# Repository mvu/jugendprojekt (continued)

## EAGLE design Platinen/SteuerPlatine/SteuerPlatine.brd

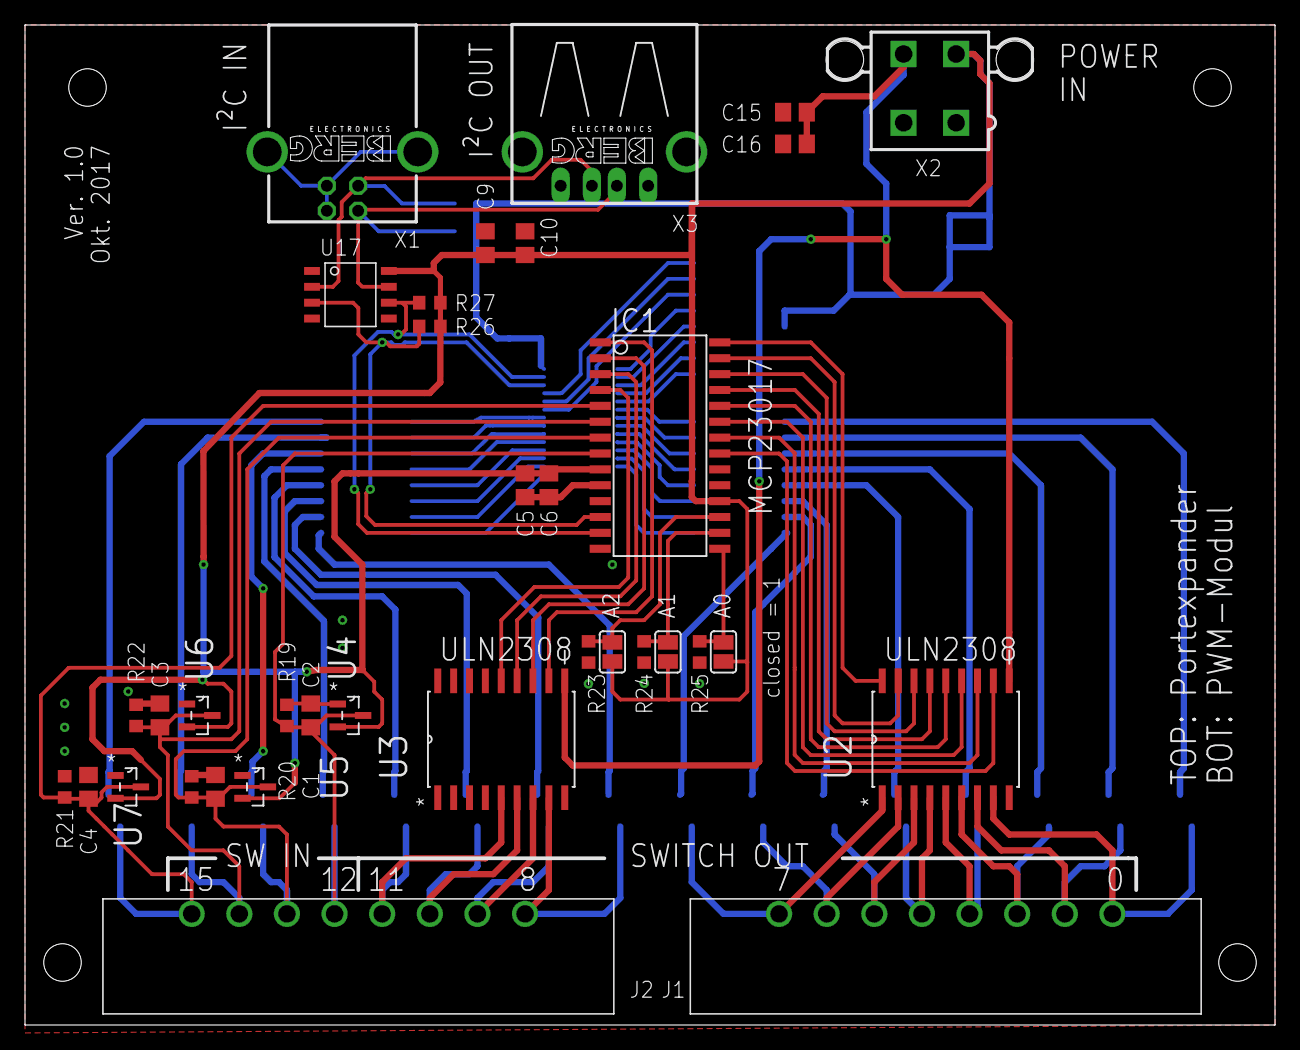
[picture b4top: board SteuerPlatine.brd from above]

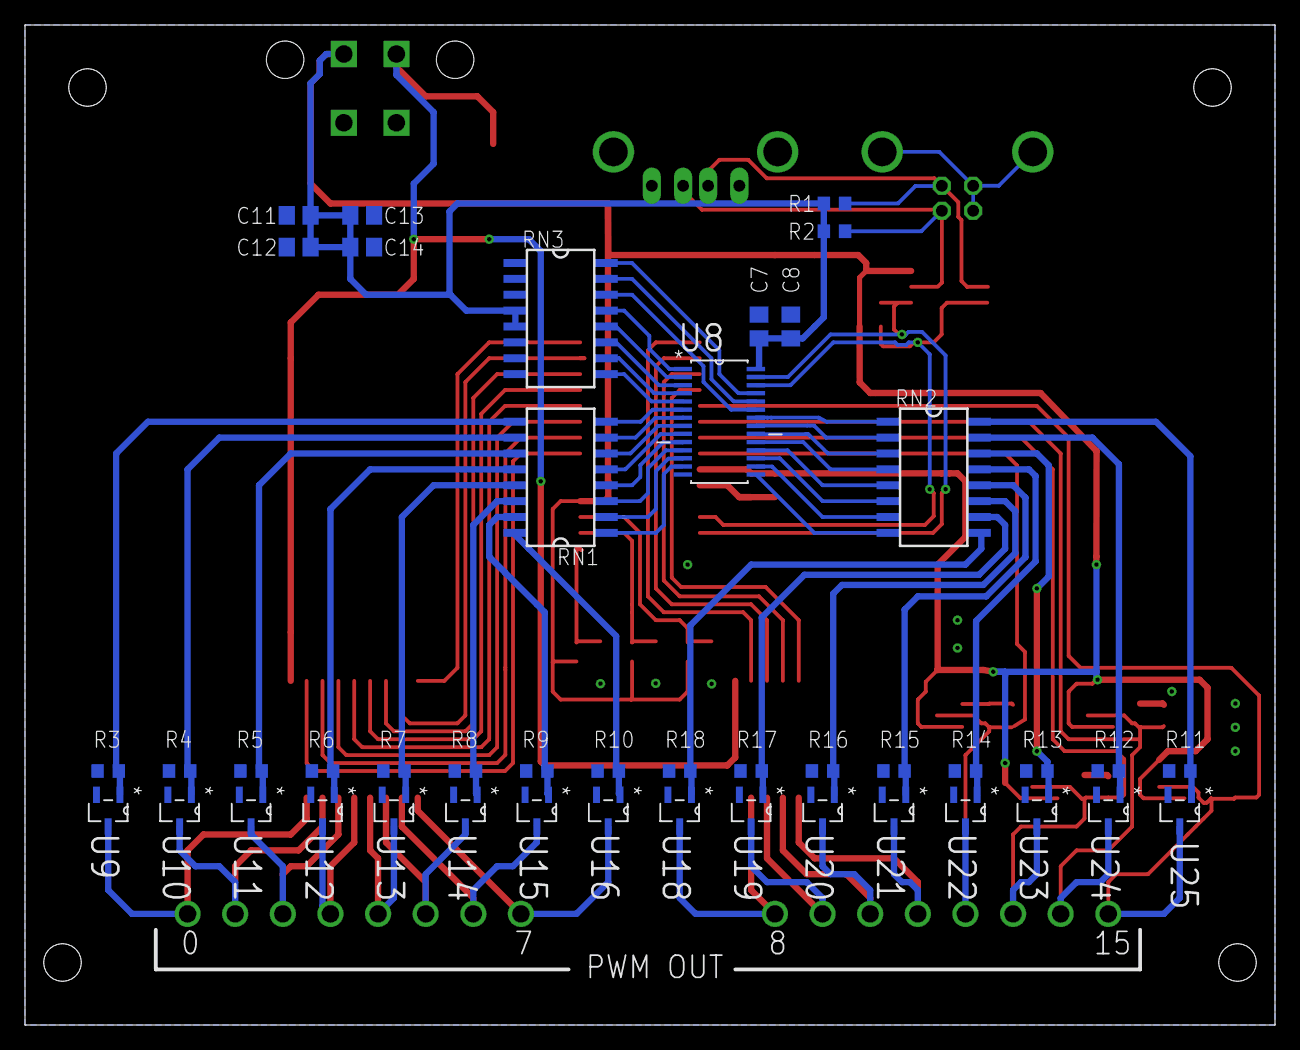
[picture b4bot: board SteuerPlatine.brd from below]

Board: 2 copper layers, 100.0 x 80.0 mm, 79 parts (44 on the bottom side), 78 nets.

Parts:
A0, A1, A2: SJ
C1, C2, C3, C4, C5, C7, C10, C11, C12, C15: 100nF; C0805
C6, C8, C9, C13, C14, C16: 10µF; C0805
IC1: MCP23017SO; SO28W
J1, J2: 691325310008
R1, R2, R3, R4, R5, R6, R7, R8, R9, R10, R11, R12, R13, R14, R15, R16, R17, R18, R26, R27: R0603
R19, R20, R21, R22, R23, R24, R25: 3k; R0603
RN1, RN2, RN3: SOMC16
U2, U3: ULN2803ADW; SOIC127P1030X265-18N
U4, U5, U6, U7: BAV99; SOT91P240X120-3N
U8: PCA9635PW; SOP65P640X110-28N
U9, U10, U11, U12, U13, U14, U15, U16, U18, U19, U20, U21, U22, U23, U24, U25: TSM2306CX; SOT95P280X130-3N
U17: P82B715TD; SOIC-8
X1: PN61729-S
X2: 5566-4
X3: PN87520-S

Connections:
+5V: A0.2, A1.2, A2.2, C5.1, C6.1, C7.1, C8.1, C9.1, C10.1, C11.2, C12.2, C13.2, C14.2, IC1.9, IC1.18, R1.1, R2.1, R26.2, R27.2, RN3.4, RN3.5, U4.2, U5.2, U6.2, U7.2, U8.28, U17.8, X2.3
+12V: C15.1, C16.1, U2.10, U3.10, X2.4
GND: C1.1, C2.1, C3.1, C4.1, C5.2, C6.2, C7.2, C8.2, C9.2, C10.2, C11.1, C12.1, C13.1, C14.1, C15.2, C16.2, IC1.10, R3.1, R4.1, R5.1, R6.1, R7.1, R8.1, R9.1, R10.1, R11.1, R12.1, R13.1, R14.1, R15.1, R16.1, R17.1, R18.1, R19.2, R20.2, R21.2, R22.2, R23.1, R24.1, R25.1, RN3.1, RN3.2, RN3.3, RN3.6, RN3.7, RN3.8, U2.9, U3.9, U4.1, U5.1, U6.1, U7.1, U8.14, U9.2, U10.2, U11.2, U12.2, U13.2, U14.2, U15.2, U16.2, U17.4, U18.2, U19.2, U20.2, U21.2, U22.2, U23.2, U24.2, U25.2, X1.1, X1.4, X1.S1, X1.S2, X2.1, X2.2
unnamed: RN2.1, U8.22
unnamed: RN2.2, U8.21
unnamed: RN2.3, U8.20
unnamed: RN2.4, U8.19
unnamed: RN2.5, U8.18
unnamed: RN2.6, U8.17
unnamed: RN2.7, U8.16
unnamed: RN2.8, U8.15
unnamed: RN1.3, U8.11
unnamed: RN1.2, U8.12
unnamed: RN1.1, U8.13
unnamed: RN1.4, U8.10
unnamed: RN1.5, U8.9
unnamed: RN1.6, U8.8
unnamed: RN1.7, U8.7
unnamed: RN1.8, U8.6
unnamed: IC1.21, U2.11
unnamed: IC1.22, U2.12
unnamed: IC1.23, U2.13
unnamed: IC1.24, U2.14
unnamed: IC1.25, U2.15
unnamed: IC1.26, U2.16
unnamed: IC1.27, U2.17
unnamed: IC1.28, U2.18
unnamed: IC1.1, U3.11
unnamed: IC1.2, U3.12
unnamed: IC1.3, U3.13
unnamed: IC1.4, U3.14
unnamed: RN3.9, U8.5
unnamed: RN3.16, U8.25
unnamed: RN3.15, U8.24
unnamed: RN3.10, U8.4
unnamed: RN3.11, U8.3
unnamed: RN3.12, U8.2
unnamed: RN3.13, U8.1
unnamed: RN3.14, U8.23
unnamed: A2.1, IC1.17, R23.2
unnamed: A1.1, IC1.16, R24.2
unnamed: A0.1, IC1.15, R25.2
unnamed: R2.2, U17.7, X1.2, X3.2
unnamed: R1.2, U17.2, X1.3, X3.3
PWM1: R3.2, RN1.9, U9.1
PWM2: R4.2, RN1.10, U10.1
PWM3: R5.2, RN1.11, U11.1
PWM4: R6.2, RN1.12, U12.1
PWM5: R7.2, RN1.13, U13.1
PWM6: R8.2, RN1.14, U14.1
PWM7: R9.2, RN1.15, U15.1
PWM8: R10.2, RN1.16, U16.1
PWM9: R18.2, RN2.9, U18.1
PWM10: R17.2, RN2.10, U19.1
PWM11: R16.2, RN2.11, U20.1
PWM12: R15.2, RN2.12, U21.1
PWM13: R14.2, RN2.13, U22.1
PWM14: R13.2, RN2.14, U23.1
PWM15: R12.2, RN2.15, U24.1
PWM16: R11.2, RN2.16, U25.1
PWM-OUT1: J1.8, U2.8, U9.3
PWM-OUT2: J1.7, U2.7, U10.3
PWM-OUT3: J1.6, U2.6, U11.3
PWM-OUT4: J1.5, U2.5, U12.3
PWM-OUT5: J1.4, U2.4, U13.3
PWM-OUT6: J1.3, U2.3, U14.3
PWM-OUT7: J1.2, U2.2, U15.3
PWM-OUT8: J1.1, U2.1, U16.3
PWM-OUT9: J2.8, U3.8, U18.3
PWM-OUT10: J2.7, U3.7, U19.3
PWM-OUT11: J2.6, U3.6, U20.3
PWM-OUT12: J2.5, U3.5, U21.3
PWM-OUT13: C2.2, IC1.8, J2.4, R19.1, U4.3, U22.3
PWM-OUT14: C1.2, IC1.7, J2.3, R20.1, U5.3, U23.3
PWM-OUT15: C3.2, IC1.6, J2.2, R22.1, U6.3, U24.3
PWM-OUT16: C4.2, IC1.5, J2.1, R21.1, U7.3, U25.3
SCL: IC1.12, R26.1, U8.26, U17.3
SDA: IC1.13, R27.1, U8.27, U17.6

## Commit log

2016-05-19 Update README.md
    voll krass new changes alter
2016-10-03 Erster commit: control panel
2016-10-03 readme angepasst
2016-10-03 readme geaendert
2017-05-18 Neuster Stand
2017-05-18 Datasheet hinzugefügt
2017-05-18 Code der Aruinos an den RGB-Stripes
2017-05-18 Das Programm der Arduinos an den RGB-Stripes
2017-05-19 Temperatur überwachung über Netzwerk
2017-05-19 Update Netzwerk mit IP vom Raspberry pi
2017-09-30 Beta Version 1.0
    ein gute lauffähiges Programm ohne Slider und Decken RGB
2017-12-12 Update
    Neue Platinen und Dokumentation
2017-12-13 alle Teile von reichelt oder Conrad
2017-12-14 Liste aktualisiert
2017-12-15 CAD-Zeichnungen für Befestigungsplatte erstellt
2017-12-15 CAD-Zeichnung für Befestigungsplatte aktualisiert
2017-12-15 Umfangreiche Neuorganisation der Ordnerstruktur
2017-12-15 Platinen als pdf exportiert
2017-12-15 minor changes
2017-12-20 Stücklist
2017-12-20 Aktualisiert
2017-12-22 Teile aktualisiert
2017-12-27 CAD Zeichnung Befestigung Portexpander erstellt
2018-01-02 Notizen hinzugefügt
2018-01-20 Simulationen hochgeladen
2018-01-20 aktuelles Programm von RaspberryPi hochgeladen
2018-02-16 Slider test mit Netzwerk über UDP
2018-05-08 Update
    Update text und Jugend 2.1
2018-05-26 Mosfet-Treiber simuliert
2018-05-26 Datenblätter hinzugefügt
2018-05-26 .lib aus gitignore entfernt, um LTSpice-Modelle zu versionieren
2018-05-27 ein paar libraries für LT-Spice hinzugefügt
2018-05-27 Mosfet Treiber Update
2018-05-27 kleinigkeiten
2018-05-27 .zip datei entpackt
2018-05-29 Teile für Mosfet-Treiber 2.0 in Bestückungsliste eingetragen
2018-05-29 Arduino-Test-Programm zur PWM-Generation hinzugefügt
2018-05-29 Mosfet-Treiber 2.0 PCB-Layout finalisiert
2018-06-04 Mosfet Treiber fertig gestellt
2018-06-05 Befestigungsloch verschoben
2018-06-05 Dateien in Ordner zusammengefasst
2018-06-05 CAD für Befestigungsplatte der Mosfet-Treiber Ver 2.0 erstellt
2018-06-05 gerber Files erzeugt
2018-06-12 Bestückungsliste für Mosfettreiber Ver. 2 erstellt
2018-07-28 Slider_UDP.ino in eigenen Ordner verschoben; Arduino IDE braucht das
2018-07-28 weitere Datenblätter hinzugefügt
2018-07-28 echte 0% Pulsbreite eingebaut
2018-07-28 Hauptlichttreiber fertig gestellt
2019-01-14 .gitignore für LT-Spice angepasst
2019-01-14 update2
2019-01-15 Grundstein für Version 3.0 gelegt
2019-01-15 Doxygen intergriert
2019-01-15 MainWindow aus altem Projekt in Startseite umgezogen
2019-01-15 Dateien nach model und view getrennt, low lvel hardware Zugriff begonnen
2019-01-15 Dokumentation um Ordner- und Dateibeschreibungen erweitert
2019-01-16 Einstellungen für QtCreator für cross-compile und ausführung via RDP
2019-01-17 .pro.shared Datei entfernt, da unnötig
2019-01-17 Bug entdeckt und kommentiert
2019-01-17 Licht- und Medien-Menü umgezogen
2019-01-17 Systemstatus GUI umgezogen
2019-01-17 EinstellungTheke-Gui umgezogen
2019-01-17 fehlende Dateien EinstellungTheke-Gui umgezogen
2019-01-17 fixed merge conflict in .pro
2019-01-17 GUI Einstellung RGB Wand umgezogen
2019-01-18 Passwort GUI umgezogen
2019-01-18 GUI für Audio-Einstellungen umgezogen
2019-01-18 fixed merge conflicts in .pro and startseite.h
2019-01-18 fixed merge conflicts for startseite.h
2019-01-18 Klasse zum Lesen und Schreiben von config-Datein hinzugefügt
2019-01-18 FileHandler am testen. Hat noch einige Bugs
2019-01-21 Fenster zur Auswahl des Speicherortes hinzugefügt
2019-01-21 Dokumentation ergänzt
2019-01-21 Icon für Teenkreis umbenannt
2019-01-21 Jugendraum model aus Passwort Klasse entfernt
2019-01-21 Speichermenü hinzugefügt
2019-01-22 STRIP_FROM_PATH gesetzt, um Ausgabe der vollen Dateipfade in den Abhängigkeitsdiagrammen zu unterdrücken.
2019-01-22 Die Lesefunktion funktioniert und wirft Fehler, falls z.B. ein falscher Typ gelesen wird
2019-01-22 Fenster für Einstellung der Hauptlichter umgezogen
2019-01-22 Klasse in EinstellungRGBWand umbenannt
2019-01-22 todo in Doku eingefügt
2019-01-22 Fenster zur Einstellung der Decken-RGBs umgezogen
2019-01-23 FileHandler fertiggebaut und getestet
2019-01-23 kleinere Schönheitkorrekturen durchgeführt
2019-01-23 neue Basisklasse für alle Jugendraum-Objekte angelegt
2019-01-24 angefangen Klasse für Paletten_Licht zu bauen. Probleme beim Aufrufen von update
2019-01-24 update-Funktion von JElement gebaut, läuft jetzt. Palettenlich als Beispiel für Verwendung
2019-01-24 JElement Lese- und Schreibfunktionen angepasst
2019-01-24 FileHandler zu JElement hinzugefügt
2019-01-24 Klasse für die Thekenlichter angelegt
2019-01-24 Basisklasse für alle RGB-Lichter gebaut
2019-01-24 Thekenlichtklasse soweit fertiggestellt. Alle Interaktionen mit der Gui fehlen noch
2019-01-24 Dokumentation erstellt oder vervollständigt
2019-01-24 Klasse für die Wand-RGBs gebaut
2019-01-24 Speicher- und Ladefunktion von WandRGB gebaut
2019-01-24 Speicher- und Ladefunktionen bei ThekenLicht, WandRGB und PalettenLicht gebaut
2019-01-28 Slider als Klasse angelegt
2019-01-28 indermediate commit
2019-01-28 Ideenfindung für Streifenmanagement beendet
2019-01-28 Include Pfade angepasst
2019-01-28 zusätzlichen Zustand in RGBElement eingefügt, der noch in allen abgeleiteten Klassen behandelt werden muss
2019-01-28 RGBElement um on/off erweitert und alle abgleiteten Klassen angepasst
2019-01-28 alle bisherigen RGB-Unterklassen an die erweiterte RGBElement angepasst
2019-01-28 Removed a lot of errors in the Slider class. working now
2019-01-28 removed Testprogramme/ from version control
2019-01-29 set-Methoden von RGBElement so weit verallgemeinert, das die abgleiteten Klassen sie nicht mehr überschreiben müssen. Entsprechend alle abgeleiteten Klassen geändert.
2019-01-29 On/Off Funktion der einzelnen Streifen gebaut
2019-01-29 Verhalten der Hauptlicht-Steuerung gebaut mit Berücksichtigung der Gruppen-Buttons. Noch nicht getestet. Slider-Integration fehlt noch
2019-01-29 Beschriftungen der An/Aus-Knöpfe wird jetzt beim Klicken umgeschaltet
2019-01-29 Läuft soweit und kann in ControlPanel-3-0 integriert werden
2019-01-30 Laufzeitmessungen durchgeführt
2019-01-30 Gruppenauswahl beim Hauptlicht gebaut und getestet
2019-01-30 Software-Slider in hauptlicht integriert. An/Aus-Knop arbeitet noch nicht
2019-01-30 fixed bug which caused slider not to move in certain cases
2019-01-30 started integration of sliders into main project
2019-02-01 Slider moves now regardless of active-flag
2019-02-01 Slider läuft soweit und kann verwendet werden
2019-02-01 Testweise Integration der Slider
2019-02-01 published UDPTerminal
2019-02-02 JTemperatureController verselbstständigt, erstmalig compiled
2019-02-02 doxygen integriert
2019-02-06 fixed merge conflict
2019-02-06 adjusted pid parameters
2019-02-06 fixed merge conflicts
2019-02-06 An/Aus-Button für das Hauptlicht ans Laufen gebracht
2019-02-06 Ein paar Bugs des An-/Aus-Buttons gefixt
2019-02-06 Klasse für RGB-Decken-Streifen angelegt
2019-02-06 Klasse weitergebaut und Member im Jugendraum angelegt
2019-02-06 TODO geändert
2019-02-06 Klasse für RGB-Streifen nochmal geändert
2019-02-06 added udp on localhost for communication with control panel
2019-02-07 set -Funktionen in RGBElement virtual gemacht und in RGBStreifen überschrieben
2019-02-07 switched to dedicated udp sockets to ensure data integrity
2019-02-07 Decken-RGB-Einstellung angefangen zu bauen. Gruppen funktionieren. Es fehlen die Slider
2019-02-07 added standby mode for sliders
2019-02-07 Thekeneinstellung fertig; debug-Ausgabe noch vorhanden
2019-02-07 Doku aktualisiert
2019-02-07 Verdunklung und Ränder der Buttons korrigiert; alles richtig jetzt
2019-02-08 Anzeige der Uhrzeit auf Startseite implementiert
2019-02-08 Im Licht-Menü Buttons korrigiert und Zeitanzeige implementiert
2019-02-08 alpha der Buttons auf 100 (normal) bzw. 150 (pressed) geändert
2019-02-08 Slider integriert, Buttons angepasst
2019-02-08 quick and dirty auto-disable für Sliderfunktionen
2019-02-08 added slider disable
2019-02-08 Im Fenster zum Speichern Änderung der Transparenz der Knöpfe bei Click eingefügt
2019-02-08 Im Menü der Medien veränderte Transparenz der Knöpfe bei Klick eingebaut; Zeitanzeige mit Leben gefüllt
2019-02-08 All configration is now read from a file
2019-02-08 Temperatur-Konfigurationswerte werden bei Temperaturabfrage mit gesendet
2019-02-08 filehandler mit QString kompatibel gemacht
2019-02-08 udp Verbindung auf localhost zu Temperatur-Service hergestellt
2019-02-08 still fixing merge problems
2019-02-08 added software slider for testing
2019-02-08 some bugs fixed. Slider work now. On-off button not
2019-02-08 einstellung_rgb_decke works no completly
2019-02-08 removed software slider that we used to test einstellung_rgb_decke
2019-02-11 Anzeige von Temperaturen und Lüftergeschwindigkeiten klappt
2019-02-11 Added pi's cpu to the observation
2019-02-11 changed default text of systems's status display so that it shows errors if the temperatur monitoring service isn't running
2019-02-11 used other sliders, hide on-off button if not usable, uncheck buttons on close
2019-02-12 einstellung_hauptlicht nach dem Vorbild von einstellung_rgb_decke schöner programmiert
2019-07-23 Auslesen der Temperatursensoren mit Arduino auf Register umgestellt
2019-07-23 IP an Jugendraum angepasst
2019-07-23 gravierende Fehler beseitigt, Temperaturüberwachung kompiliert läuft soweit
2019-07-23 CLI für jugendraum begonnen
2019-07-24 fixed bugs, fan control now working
2019-07-24 minor renaming to clarify
2019-07-24 added logging functionality, adjusted hardware configuration, removed debug outputs on release
2019-07-24 created a system service for temperature
2019-09-10 some libraries for special parts added
2019-09-10 corrected table layout
2019-10-26 ordered sources and headers alphabetically
2019-10-26 added config to remove debug output on release build
2019-10-27 changed logfile location to /var/log/jugendraum/temperature.log
2019-10-27 disabled wiringPi functionality for testing on bare pi
2019-10-27 todo added
2019-10-27 changed order of destroying child objects
2019-10-27 fixed line endings
2019-10-27 added logging functionality
2019-10-27 added variable to indicate temperature service is not responding
2019-10-27 minor changes and commenting
2019-10-28 added missing write functions. Still bugs present
